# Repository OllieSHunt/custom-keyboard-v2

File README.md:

# Custom Keyboard V2
This repository contains KiCad design files for a home-made custom keyboard.

## Current State
***IMPORTANT***: Although the keymap reference sheet (`./keymap/keymap-exported.pdf`) mentions a "Stenotype mode", this is not yet implemented. The rest of the keyboard should be fully functioning though.

## Key Features
- Support for both QWERTY and Dvorak layouts
- Stenography support (**WIP**)
- 128x64 OLED display
  - WPM counter
  - Visual indicators for caps lock, num lock, and scroll lock, as well as layers
- RGB lighting with cool animations

## Repository Layout
- `./circit_board` = KiCad design files
- `./kicad-libs` = Third party libraries that KiCad can use
- `./keymap` = Reference sheet of this keyboard's layout (**NOTE**: `keymap-inkscape.svg` will only show both pages properly when opened with [Inkscape](https://inkscape.org). If you don't want to download Inkscape, please see `keymap-exported.pdf` instead)

## QMK Firmware
This repository just contains the KiCad design files. For the firmware, see [my fork of QMK](https://github.com/OllieSHunt/qmk_firmware).

**IMPORTANT**: Within the fork, the firmware for this keyboard will be located in `dev_branch`, **not** the default `master` branch and will be under the folder `keyboards/custom_keyboard_v2`.

Useful QMK links:
- https://docs.qmk.fm/newbs
- https://docs.qmk.fm/newbs_git_best_practices

## Components List
- Custom circuit board
- Raspberry Pi Pico 1 (without headers)
- SSD1306 based 128x64 OLED display (must be I2C compatible and run of 3V)
- 46 Gateron Low Profile Switch 2.0
- 46 Gateron compatible Low Profile Keycaps
- 46 1N4148W diodes
- 46 WS2812C-2020 LEDs
- Some stick-on silicone feet (I used 5mm tall ones)

## KiCad Libraries Used
- [MX_V2](https://github.com/ai03-2725/MX_V2/tree/main)

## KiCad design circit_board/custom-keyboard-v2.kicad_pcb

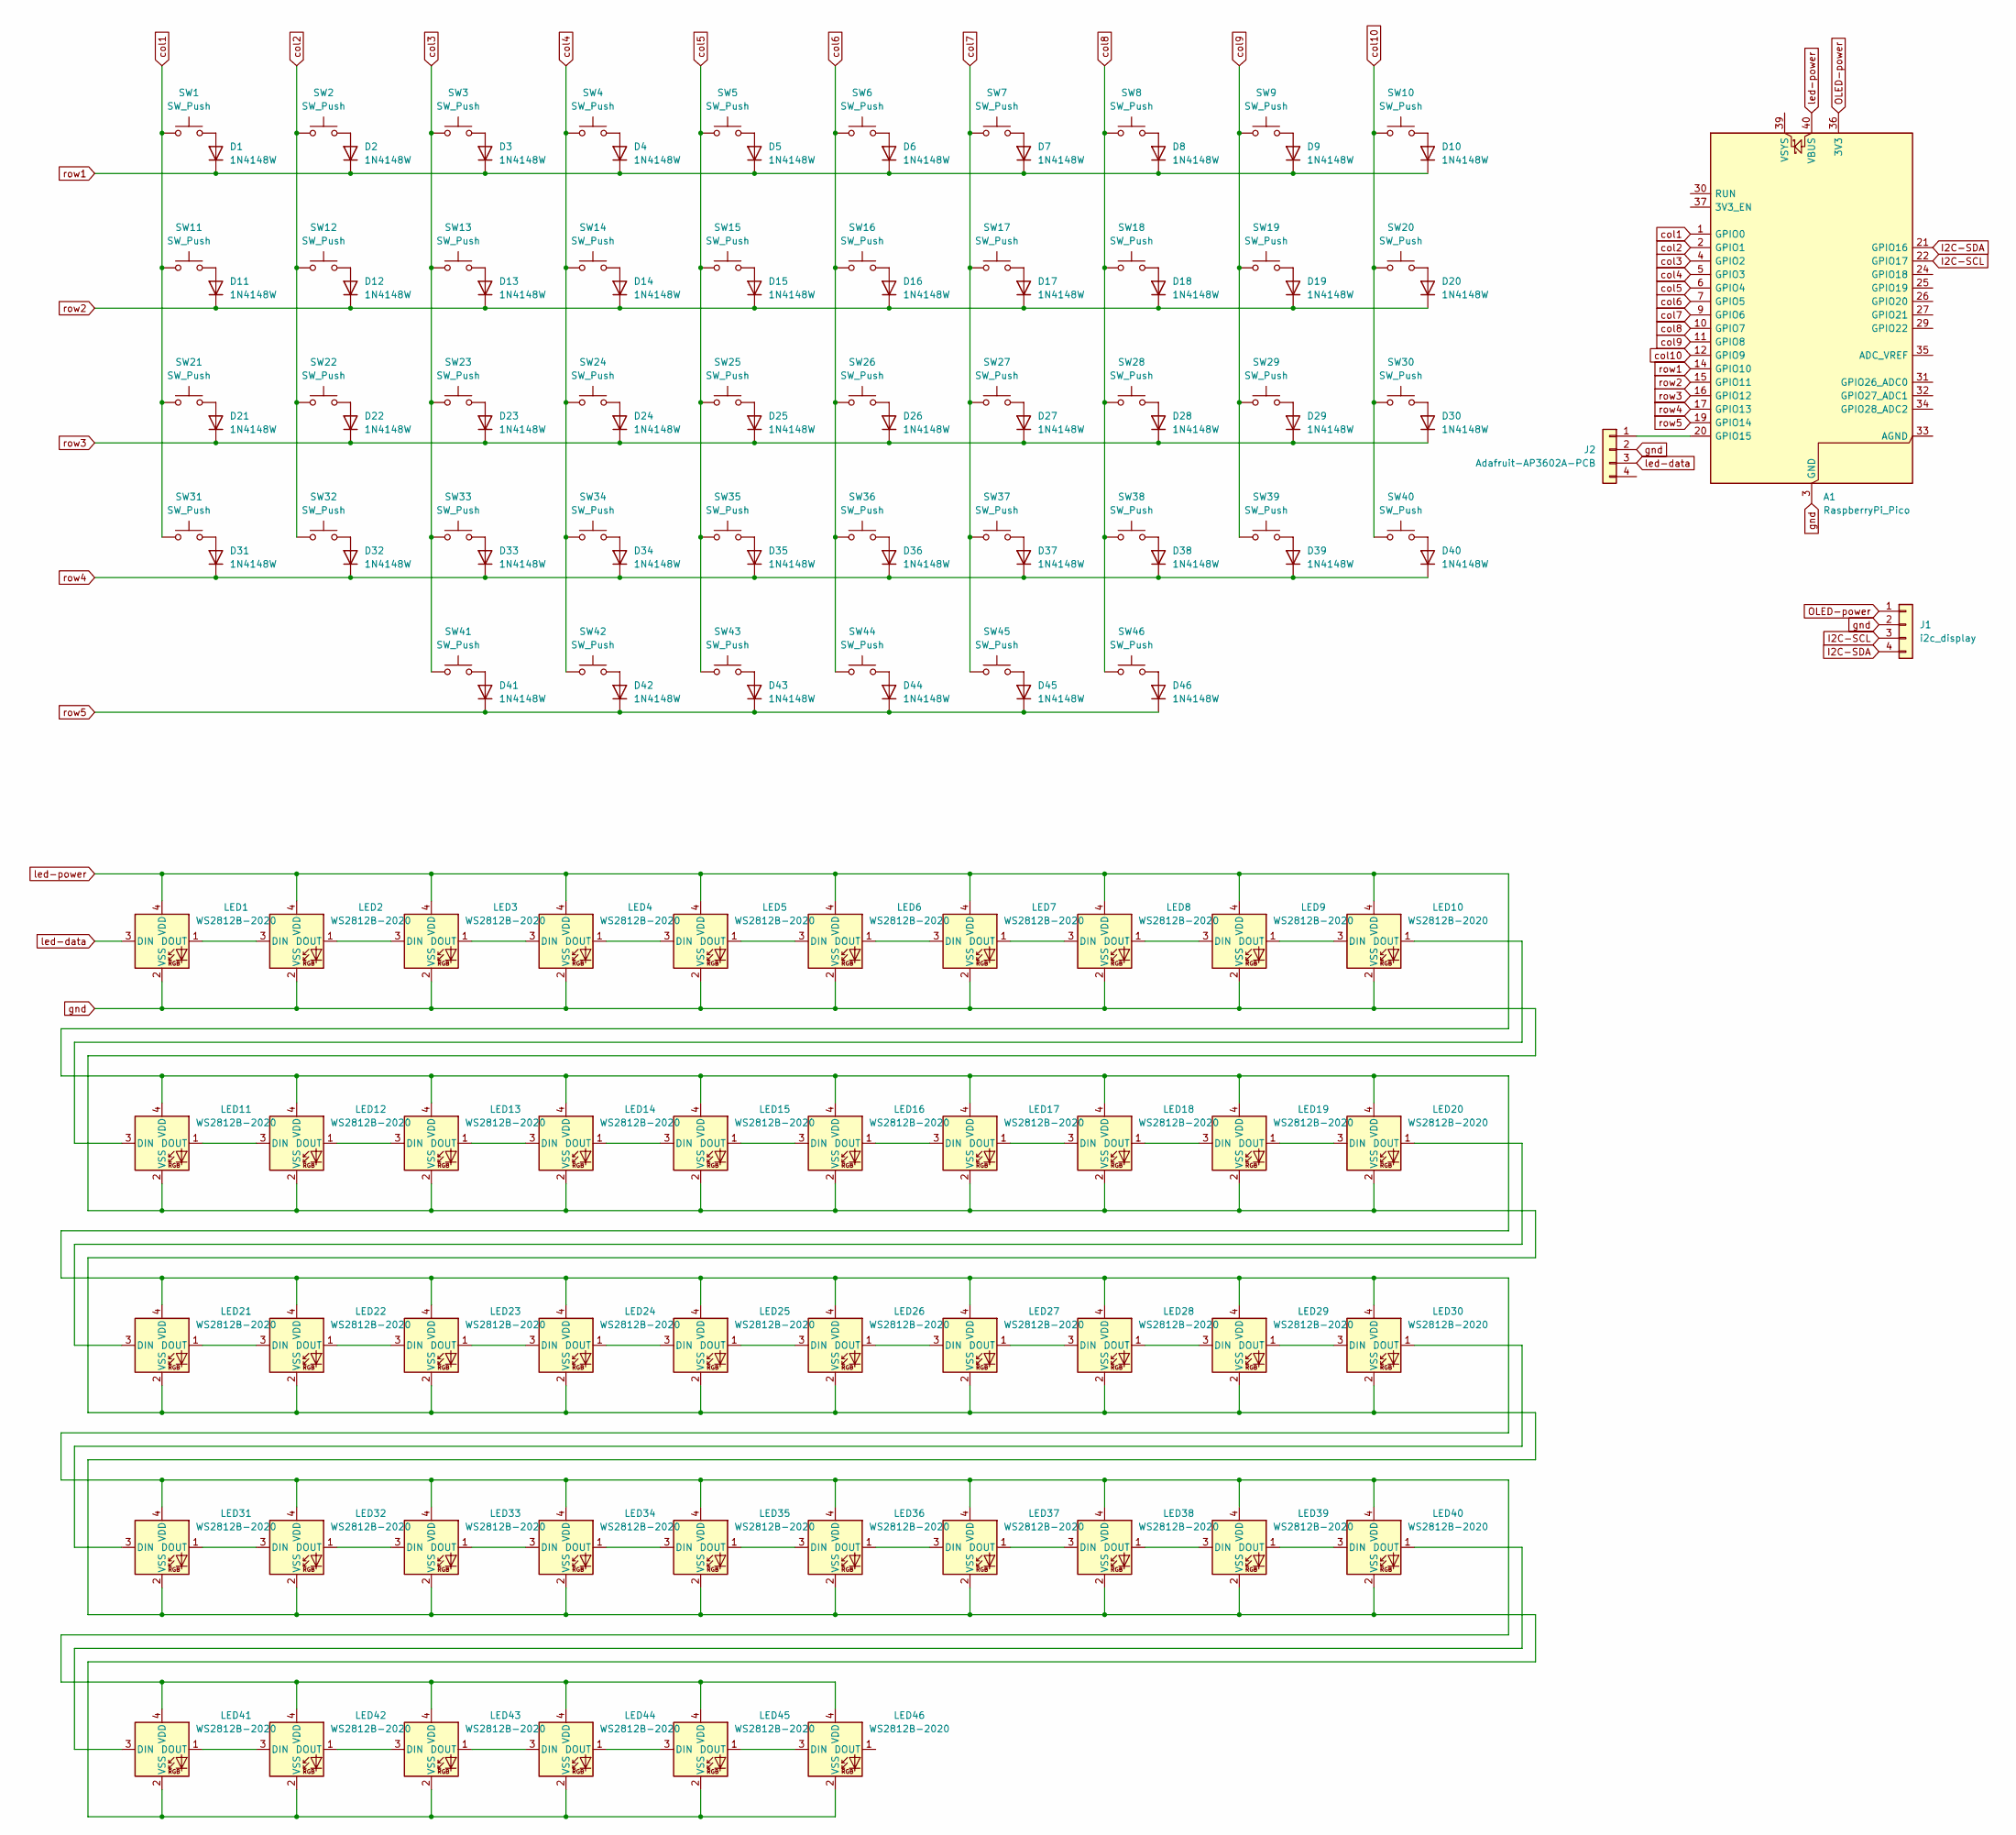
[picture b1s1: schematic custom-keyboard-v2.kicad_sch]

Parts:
A1: RaspberryPi_Pico; RaspberryPi_Pico_Common_SMD
D1, D2, D3, D4, D5, D6, D7, D8, D9, D10, D11, D12, D13, D14, D15, D16, D17, D18, D19, D20, D21, D22, D23, D24, D25, D26, D27, D28, D29, D30, D31, D32, D33, D34, D35, D36, D37, D38, D39, D40, D41, D42, D43, D44, D45, D46: 1N4148W; D_SOD-123
J1: i2c_display; PinHeader_1x04_P2.54mm_Vertical
J2: Adafruit-AP3602A-PCB; PinHeader_1x04_P2.54mm_Vertical
LED1, LED2, LED3, LED4, LED5, LED6, LED7, LED8, LED9, LED10, LED11, LED12, LED13, LED14, LED15, LED16, LED17, LED18, LED19, LED20, LED21, LED22, LED23, LED24, LED25, LED26, LED27, LED28, LED29, LED30, LED31, LED32, LED33, LED34, LED35, LED36, LED37, LED38, LED39, LED40, LED41, LED42, LED43, LED44, LED45, LED46: WS2812B-2020; LED_WS2812B-2020_PLCC4_2.0x2.0mm
SW1, SW2, SW3, SW4, SW5, SW6, SW7, SW8, SW9, SW10, SW11, SW12, SW13, SW14, SW15, SW16, SW17, SW18, SW19, SW20, SW21, SW22, SW23, SW24, SW25, SW26, SW27, SW28, SW29, SW30, SW31, SW32, SW33, SW34, SW35, SW36, SW37, SW38, SW39, SW40, SW41, SW42, SW43, SW44, SW45, SW46: SW_Push; Gateron-KS33-Solderable-Template

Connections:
I2C-SCL: A1.22 (GPIO17), J1.3
I2C-SDA: A1.21 (GPIO16), J1.4
unnamed: D1.2 (A), SW1.2
unnamed: D2.2 (A), SW2.2
unnamed: D3.2 (A), SW3.2
unnamed: D4.2 (A), SW4.2
unnamed: D5.2 (A), SW5.2
unnamed: D6.2 (A), SW6.2
unnamed: D7.2 (A), SW7.2
unnamed: D8.2 (A), SW8.2
unnamed: D9.2 (A), SW9.2
unnamed: D10.2 (A), SW10.2
unnamed: D11.2 (A), SW11.2
unnamed: D12.2 (A), SW12.2
unnamed: D13.2 (A), SW13.2
unnamed: D14.2 (A), SW14.2
unnamed: D15.2 (A), SW15.2
unnamed: D16.2 (A), SW16.2
unnamed: D17.2 (A), SW17.2
unnamed: D18.2 (A), SW18.2
unnamed: D19.2 (A), SW19.2
unnamed: D20.2 (A), SW20.2
unnamed: D21.2 (A), SW21.2
unnamed: D22.2 (A), SW22.2
unnamed: D23.2 (A), SW23.2
unnamed: D24.2 (A), SW24.2
unnamed: D25.2 (A), SW25.2
unnamed: D26.2 (A), SW26.2
unnamed: D27.2 (A), SW27.2
unnamed: D28.2 (A), SW28.2
unnamed: D29.2 (A), SW29.2
unnamed: D30.2 (A), SW30.2
unnamed: D31.2 (A), SW31.2
unnamed: D32.2 (A), SW32.2
unnamed: D33.2 (A), SW33.2
unnamed: D34.2 (A), SW34.2
unnamed: D35.2 (A), SW35.2
unnamed: D36.2 (A), SW36.2
unnamed: D37.2 (A), SW37.2
unnamed: D38.2 (A), SW38.2
unnamed: D39.2 (A), SW39.2
unnamed: D40.2 (A), SW40.2
unnamed: D41.2 (A), SW41.2
unnamed: D42.2 (A), SW42.2
unnamed: D43.2 (A), SW43.2
unnamed: D44.2 (A), SW44.2
unnamed: D45.2 (A), SW45.2
unnamed: D46.2 (A), SW46.2
unnamed: LED1.1 (DOUT), LED2.3 (DIN)
unnamed: LED2.1 (DOUT), LED3.3 (DIN)
unnamed: LED3.1 (DOUT), LED4.3 (DIN)
unnamed: LED4.1 (DOUT), LED5.3 (DIN)
unnamed: LED5.1 (DOUT), LED6.3 (DIN)
unnamed: LED6.1 (DOUT), LED7.3 (DIN)
unnamed: LED7.1 (DOUT), LED8.3 (DIN)
unnamed: LED8.1 (DOUT), LED9.3 (DIN)
unnamed: LED9.1 (DOUT), LED10.3 (DIN)
unnamed: LED10.1 (DOUT), LED11.3 (DIN)
unnamed: LED11.1 (DOUT), LED12.3 (DIN)
unnamed: LED12.1 (DOUT), LED13.3 (DIN)
unnamed: LED13.1 (DOUT), LED14.3 (DIN)
unnamed: LED14.1 (DOUT), LED15.3 (DIN)
unnamed: LED15.1 (DOUT), LED16.3 (DIN)
unnamed: LED16.1 (DOUT), LED17.3 (DIN)
unnamed: LED17.1 (DOUT), LED18.3 (DIN)
unnamed: LED18.1 (DOUT), LED19.3 (DIN)
unnamed: LED19.1 (DOUT), LED20.3 (DIN)
unnamed: LED20.1 (DOUT), LED21.3 (DIN)
unnamed: LED21.1 (DOUT), LED22.3 (DIN)
unnamed: LED22.1 (DOUT), LED23.3 (DIN)
unnamed: LED23.1 (DOUT), LED24.3 (DIN)
unnamed: LED24.1 (DOUT), LED25.3 (DIN)
unnamed: LED25.1 (DOUT), LED26.3 (DIN)
unnamed: LED26.1 (DOUT), LED27.3 (DIN)
unnamed: LED27.1 (DOUT), LED28.3 (DIN)
unnamed: LED28.1 (DOUT), LED29.3 (DIN)
unnamed: LED29.1 (DOUT), LED30.3 (DIN)
unnamed: LED30.1 (DOUT), LED31.3 (DIN)
unnamed: LED31.1 (DOUT), LED32.3 (DIN)
unnamed: LED32.1 (DOUT), LED33.3 (DIN)
unnamed: LED33.1 (DOUT), LED34.3 (DIN)
unnamed: LED34.1 (DOUT), LED35.3 (DIN)
unnamed: LED35.1 (DOUT), LED36.3 (DIN)
unnamed: LED36.1 (DOUT), LED37.3 (DIN)
unnamed: LED37.1 (DOUT), LED38.3 (DIN)
unnamed: LED38.1 (DOUT), LED39.3 (DIN)
unnamed: LED39.1 (DOUT), LED40.3 (DIN)
unnamed: LED40.1 (DOUT), LED41.3 (DIN)
unnamed: LED41.1 (DOUT), LED42.3 (DIN)
unnamed: LED42.1 (DOUT), LED43.3 (DIN)
unnamed: LED43.1 (DOUT), LED44.3 (DIN)
unnamed: LED44.1 (DOUT), LED45.3 (DIN)
unnamed: LED45.1 (DOUT), LED46.3 (DIN)
OLED-power: A1.36 (3V3), J1.1
col1: A1.1 (GPIO0), SW1.1, SW11.1, SW21.1, SW31.1
col2: A1.2 (GPIO1), SW2.1, SW12.1, SW22.1, SW32.1
col3: A1.4 (GPIO2), SW3.1, SW13.1, SW23.1, SW33.1, SW41.1
col4: A1.5 (GPIO3), SW4.1, SW14.1, SW24.1, SW34.1, SW42.1
col5: A1.6 (GPIO4), SW5.1, SW15.1, SW25.1, SW35.1, SW43.1
col6: A1.7 (GPIO5), SW6.1, SW16.1, SW26.1, SW36.1, SW44.1
col7: A1.9 (GPIO6), SW7.1, SW17.1, SW27.1, SW37.1, SW45.1
col8: A1.10 (GPIO7), SW8.1, SW18.1, SW28.1, SW38.1, SW46.1
col9: A1.11 (GPIO8), SW9.1, SW19.1, SW29.1, SW39.1
col10: A1.12 (GPIO9), SW10.1, SW20.1, SW30.1, SW40.1
gnd: A1.3 (GND), A1.8 (GND), A1.13 (GND), A1.18 (GND), A1.23 (GND), A1.28 (GND), A1.38 (GND), J1.2, J2.2, LED1.2 (VSS), LED2.2 (VSS), LED3.2 (VSS), LED4.2 (VSS), LED5.2 (VSS), LED6.2 (VSS), LED7.2 (VSS), LED8.2 (VSS), LED9.2 (VSS), LED10.2 (VSS), LED11.2 (VSS), LED12.2 (VSS), LED13.2 (VSS), LED14.2 (VSS), LED15.2 (VSS), LED16.2 (VSS), LED17.2 (VSS), LED18.2 (VSS), LED19.2 (VSS), LED20.2 (VSS), LED21.2 (VSS), LED22.2 (VSS), LED23.2 (VSS), LED24.2 (VSS), LED25.2 (VSS), LED26.2 (VSS), LED27.2 (VSS), LED28.2 (VSS), LED29.2 (VSS), LED30.2 (VSS), LED31.2 (VSS), LED32.2 (VSS), LED33.2 (VSS), LED34.2 (VSS), LED35.2 (VSS), LED36.2 (VSS), LED37.2 (VSS), LED38.2 (VSS), LED39.2 (VSS), LED40.2 (VSS), LED41.2 (VSS), LED42.2 (VSS), LED43.2 (VSS), LED44.2 (VSS), LED45.2 (VSS), LED46.2 (VSS)
led-data: A1.20 (GPIO15), J2.1, J2.3, LED1.3 (DIN)
led-power: A1.40 (VBUS), LED1.4 (VDD), LED2.4 (VDD), LED3.4 (VDD), LED4.4 (VDD), LED5.4 (VDD), LED6.4 (VDD), LED7.4 (VDD), LED8.4 (VDD), LED9.4 (VDD), LED10.4 (VDD), LED11.4 (VDD), LED12.4 (VDD), LED13.4 (VDD), LED14.4 (VDD), LED15.4 (VDD), LED16.4 (VDD), LED17.4 (VDD), LED18.4 (VDD), LED19.4 (VDD), LED20.4 (VDD), LED21.4 (VDD), LED22.4 (VDD), LED23.4 (VDD), LED24.4 (VDD), LED25.4 (VDD), LED26.4 (VDD), LED27.4 (VDD), LED28.4 (VDD), LED29.4 (VDD), LED30.4 (VDD), LED31.4 (VDD), LED32.4 (VDD), LED33.4 (VDD), LED34.4 (VDD), LED35.4 (VDD), LED36.4 (VDD), LED37.4 (VDD), LED38.4 (VDD), LED39.4 (VDD), LED40.4 (VDD), LED41.4 (VDD), LED42.4 (VDD), LED43.4 (VDD), LED44.4 (VDD), LED45.4 (VDD), LED46.4 (VDD)
row1: A1.14 (GPIO10), D1.1 (K), D2.1 (K), D3.1 (K), D4.1 (K), D5.1 (K), D6.1 (K), D7.1 (K), D8.1 (K), D9.1 (K), D10.1 (K)
row2: A1.15 (GPIO11), D11.1 (K), D12.1 (K), D13.1 (K), D14.1 (K), D15.1 (K), D16.1 (K), D17.1 (K), D18.1 (K), D19.1 (K), D20.1 (K)
row3: A1.16 (GPIO12), D21.1 (K), D22.1 (K), D23.1 (K), D24.1 (K), D25.1 (K), D26.1 (K), D27.1 (K), D28.1 (K), D29.1 (K), D30.1 (K)
row4: A1.17 (GPIO13), D31.1 (K), D32.1 (K), D33.1 (K), D34.1 (K), D35.1 (K), D36.1 (K), D37.1 (K), D38.1 (K), D39.1 (K), D40.1 (K)
row5: A1.19 (GPIO14), D41.1 (K), D42.1 (K), D43.1 (K), D44.1 (K), D45.1 (K), D46.1 (K)

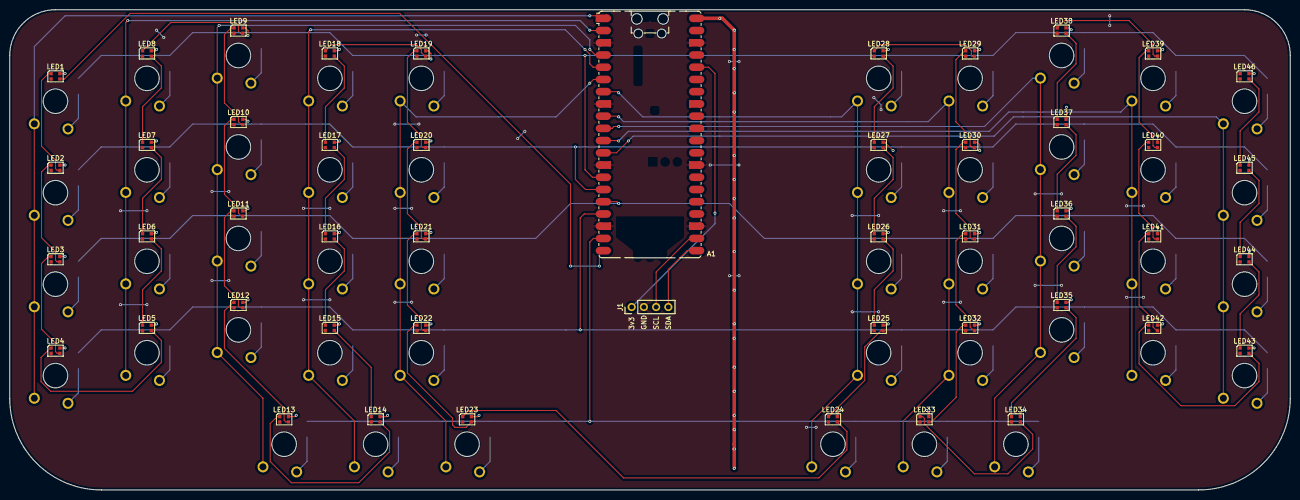
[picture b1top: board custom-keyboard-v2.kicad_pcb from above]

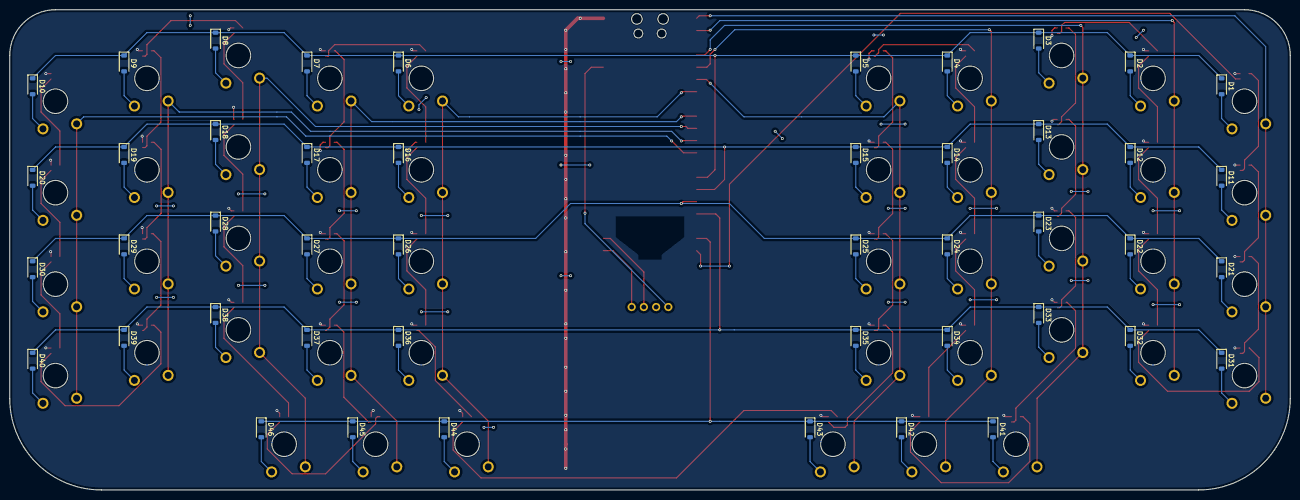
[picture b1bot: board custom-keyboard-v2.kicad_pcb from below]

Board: 2 copper layers, 266.0 x 99.8 mm, 140 parts (46 on the bottom side), 112 nets.

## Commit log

2025-06-01 Added components list
2025-06-01 Added kicad files
2025-06-01 Added kicad library for key switches + added a few components into the design
2025-06-01 Added instructions for centering an LED + gitignore
2025-06-02 Added keyboard matrix to circit schematic
2025-06-06 Added chain of LEDs intended to go under the keys to the schematic
2025-06-07 LEDs now get power from the Pi Pico's VBUS pin
2025-06-07 Possitioned keys on circitboard with spacing of 19mm (may change later)
2025-06-10 Positioned dioes on circit board
2025-06-11 Added vertical offset to keys
2025-06-11 Added edge cuts + repositioned pi pico
2025-06-11 Positioned the LEDs on the PCB
2025-06-11 Updated the componets list
2025-06-11 Added I2C OLED display
2025-06-12 Began wiring the keyboard matrix, got distracted by 3v -> 5v converters
2025-06-12 Added 3V -> 5V converter for LED data line
2025-06-12 Swaped 3V -> 5V convert from through-hole to SMT pads
2025-06-12 Key switch matrix fully routed
2025-06-12 Added ground plane
2025-06-13 Wired up the OLED display
2025-06-13 Connected LED chain data pins
2025-06-13 Powered LEDs by flooding the back layer with copper
2025-06-13 Increased silkscreen line thickness (as per jlcdfm.com's recomendation)
2025-06-14 Improved gitignore
    https://github.com/github/gitignore/blob/main/KiCad.gitignore
2025-06-18 Updated README.md with info on the QMK firmware
2025-07-02 Removed 3.3V to 5V converter from the LED input
    This turned out to be unnecessary after getting the circit board printed
2025-07-02 Added image to README.md + other misc README.md changes
2025-07-02 Create LICENSE
2025-07-02 Added list of key features to the project's README.md
2025-07-04 Updated keyboard photo in README.md
2025-07-05 Added a keymap reference sheet
2025-07-05 Made it clearer that keymap.svg will only work correctly in Inkscape
    This is because multiple pages is not supported in the svg standard.
    From the Inkscape wiki (https://wiki.inkscape.org/wiki/Multipage):
    "Pages are saved to an SVG document in the namedview tag as custom,
    Inkscape-specific elements (which do not work on the web and are not
    part of the SVG standard)."
2025-08-24 Added .png version of key map document
2025-08-24 Update README.md to show the keyboard's layout
